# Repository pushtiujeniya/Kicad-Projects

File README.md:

# Kicad-Projects
This repository contains  some 2 layer of PCB module board schematic and layout files designed using kicad software

# BME280 module board
- BME280 module measures pressure, temperature humidity, two mode interface one is I2C and other is SPI so in this design BME280 is interfaced by I2C mode.
- 3.3V DC power supply for operating the board

# DAC module board
- Digital to analog converter using MCP4721 ic
- pull up resistors for i2c  communication protocol SDA and SCL lines
- decoupling capacitor at ouput voltage
- decoupling capacitors at input voltage used MLCC and tantalum as it has low ESR
- 1X5 pin through hole connector to connect the module with controller

# LDO voltage regulator
- AMS1117-3.3V ldo regulator convert 5V DC to 3.3V DC
- Two 1x02 connector for vin and vout
- led indication for voltage input with pretected by 1Kohm resistor
- decoupling capacitor  at voltage input and voltage output

# DHT11  module
- This  module measures the temperature and  humidity value
- DHT11 sensor (input voltage range 3.3V DC to 5.5V DC)
- 3 pin header conenctor for vcc, gnd and data line
- power on led indication with  resistor protection

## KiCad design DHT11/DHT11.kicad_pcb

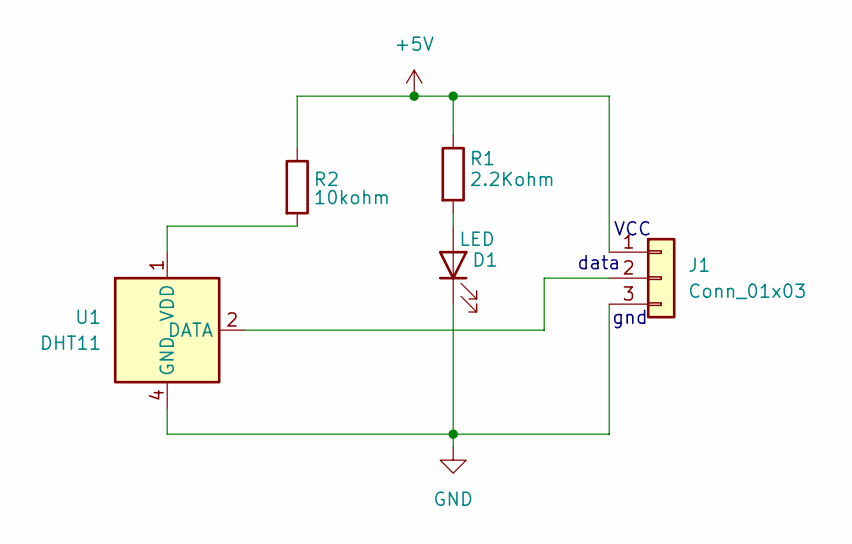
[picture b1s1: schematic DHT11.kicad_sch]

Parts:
D1: LED; LED_0603_1608Metric
J1: Conn_01x03; PinHeader_1x03_P2.54mm_Horizontal
R1: 2.2Kohm; R_0603_1608Metric
R2: 10kohm; R_0603_1608Metric
U1: DHT11; Aosong_DHT11_5.5x12.0_P2.54mm

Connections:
+5V: J1.1, R1.1, R2.1
GND: D1.1 (K), J1.3, U1.4 (GND)
unnamed: D1.2 (A), R1.2
unnamed: J1.2, U1.2 (DATA)
unnamed: R2.2, U1.1 (VDD)

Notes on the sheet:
data
gnd
VCC

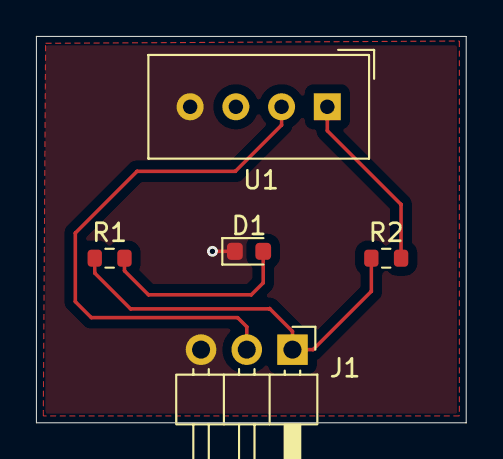
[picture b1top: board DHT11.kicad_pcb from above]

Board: 2 copper layers, 23.9 x 21.5 mm, 5 parts (0 on the bottom side), 5 nets.

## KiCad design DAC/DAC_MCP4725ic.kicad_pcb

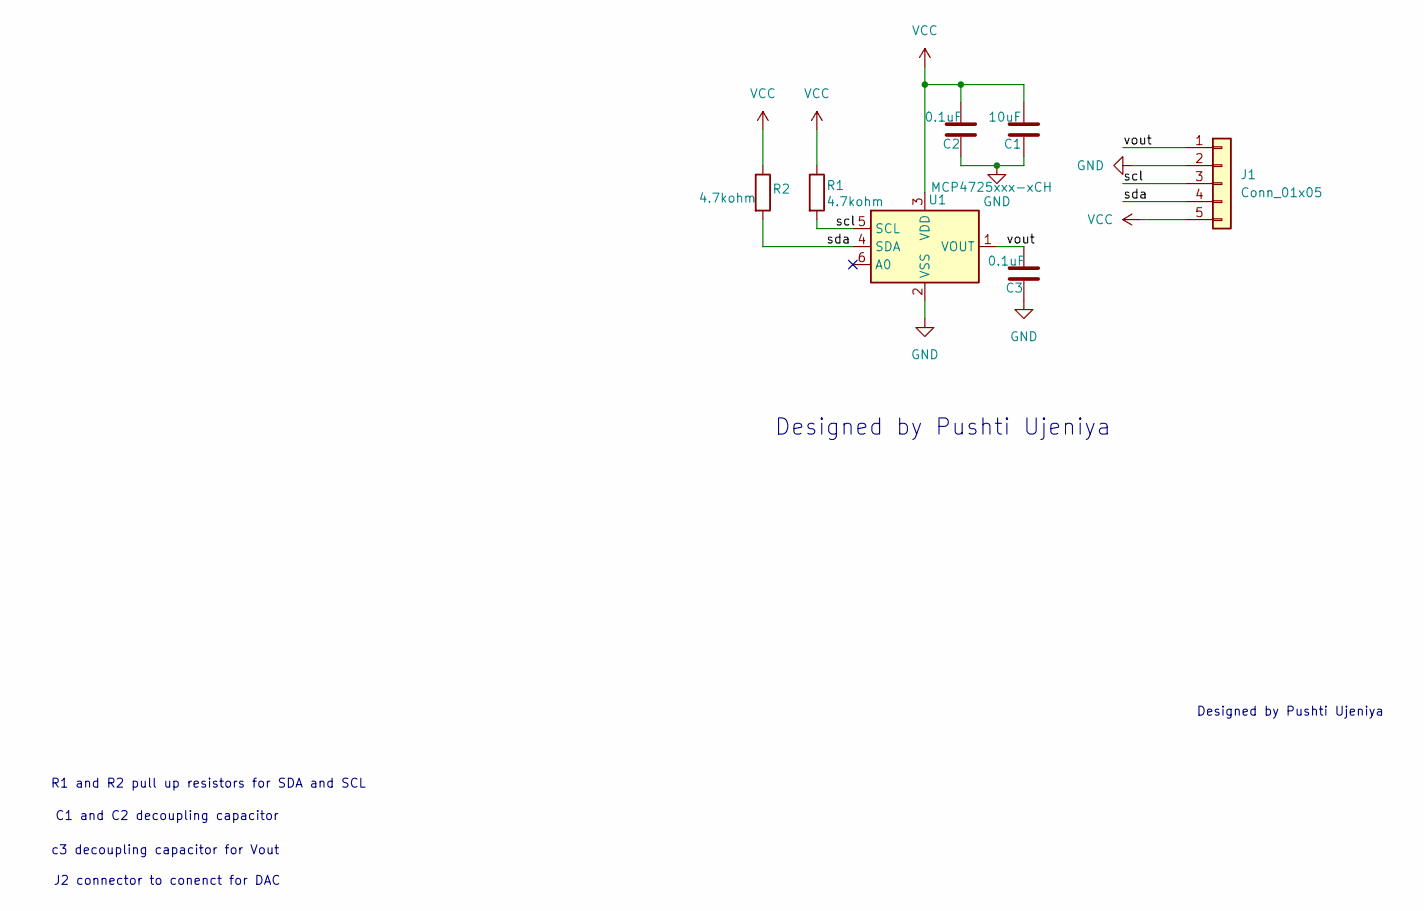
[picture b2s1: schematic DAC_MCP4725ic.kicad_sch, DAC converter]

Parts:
C1: 10uF; CP_EIA-1608-08_AVX-J
C2, C3: 0.1uF; C_0201_0603Metric
J1: Conn_01x05; PinHeader_1x05_P2.54mm_Vertical
R1, R2: 4.7kohm; R_0201_0603Metric
U1: MCP4725xxx-xCH; SOT-23-6

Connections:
/scl: J1.3, R1.2, U1.5 (SCL)
/sda: J1.4, R2.2, U1.4 (SDA)
/vout: C3.2, J1.1, U1.1 (VOUT)
GND: C1.1, C2.1, C3.1, J1.2, U1.2 (VSS)
VCC: C1.2, C2.2, J1.5, R1.1, R2.1, U1.3 (VDD)

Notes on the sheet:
Designed by Pushti Ujeniya
C1 and C2 decoupling capacitor
c3 decoupling capacitor for Vout
J2 connector to conenct for DAC
R1 and R2 pull up resistors for SDA and SCL

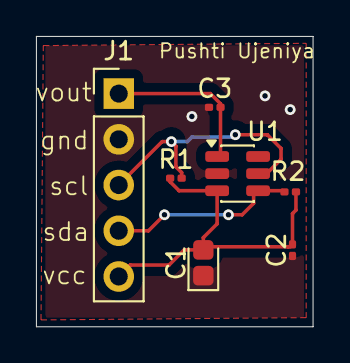
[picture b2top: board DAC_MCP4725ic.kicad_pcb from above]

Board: 2 copper layers, 15.4 x 16.1 mm, 7 parts (0 on the bottom side), 5 nets.

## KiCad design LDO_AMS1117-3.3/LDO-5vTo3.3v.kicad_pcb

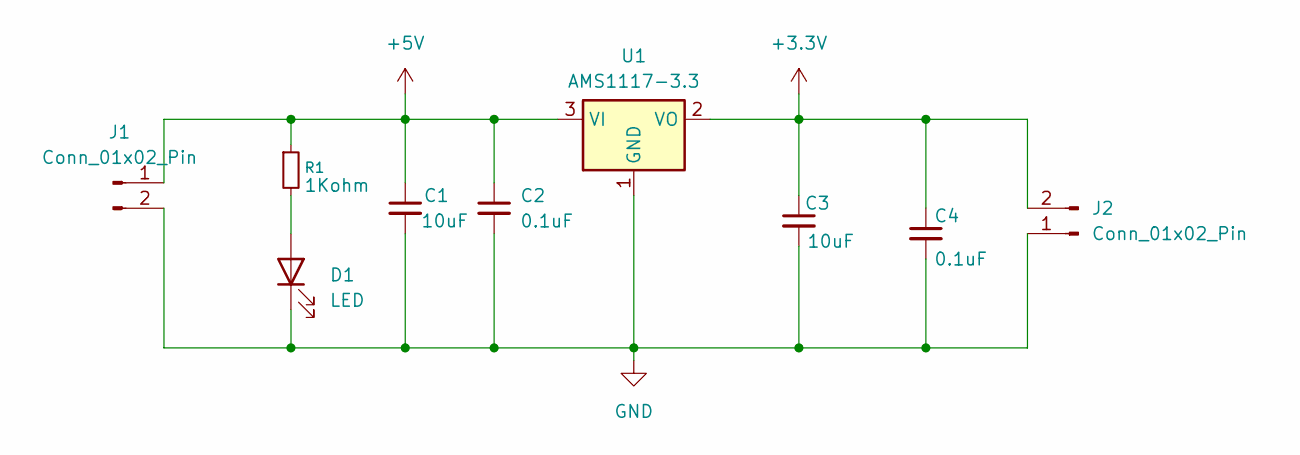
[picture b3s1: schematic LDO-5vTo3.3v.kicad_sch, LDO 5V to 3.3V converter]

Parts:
C1, C3: 10uF; C_0603_1608Metric
C2, C4: 0.1uF; C_0603_1608Metric
D1: LED; LED_0603_1608Metric
J1, J2: Conn_01x02_Pin; PinHeader_1x02_P1.00mm_Vertical
R1: 1Kohm; R_0603_1608Metric
U1: AMS1117-3.3; SOT-223-3_TabPin2

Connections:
+3.3V: C3.1, C4.1, J2.2, U1.2 (VO)
+5V: C1.1, C2.1, J1.1, R1.1, U1.3 (VI)
GND: C1.2, C2.2, C3.2, C4.2, D1.1 (K), J1.2, J2.1, U1.1 (GND)
unnamed: D1.2 (A), R1.2

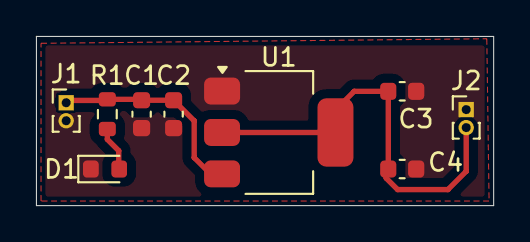
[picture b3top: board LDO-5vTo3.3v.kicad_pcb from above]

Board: 2 copper layers, 25.4 x 9.4 mm, 9 parts (0 on the bottom side), 4 nets.

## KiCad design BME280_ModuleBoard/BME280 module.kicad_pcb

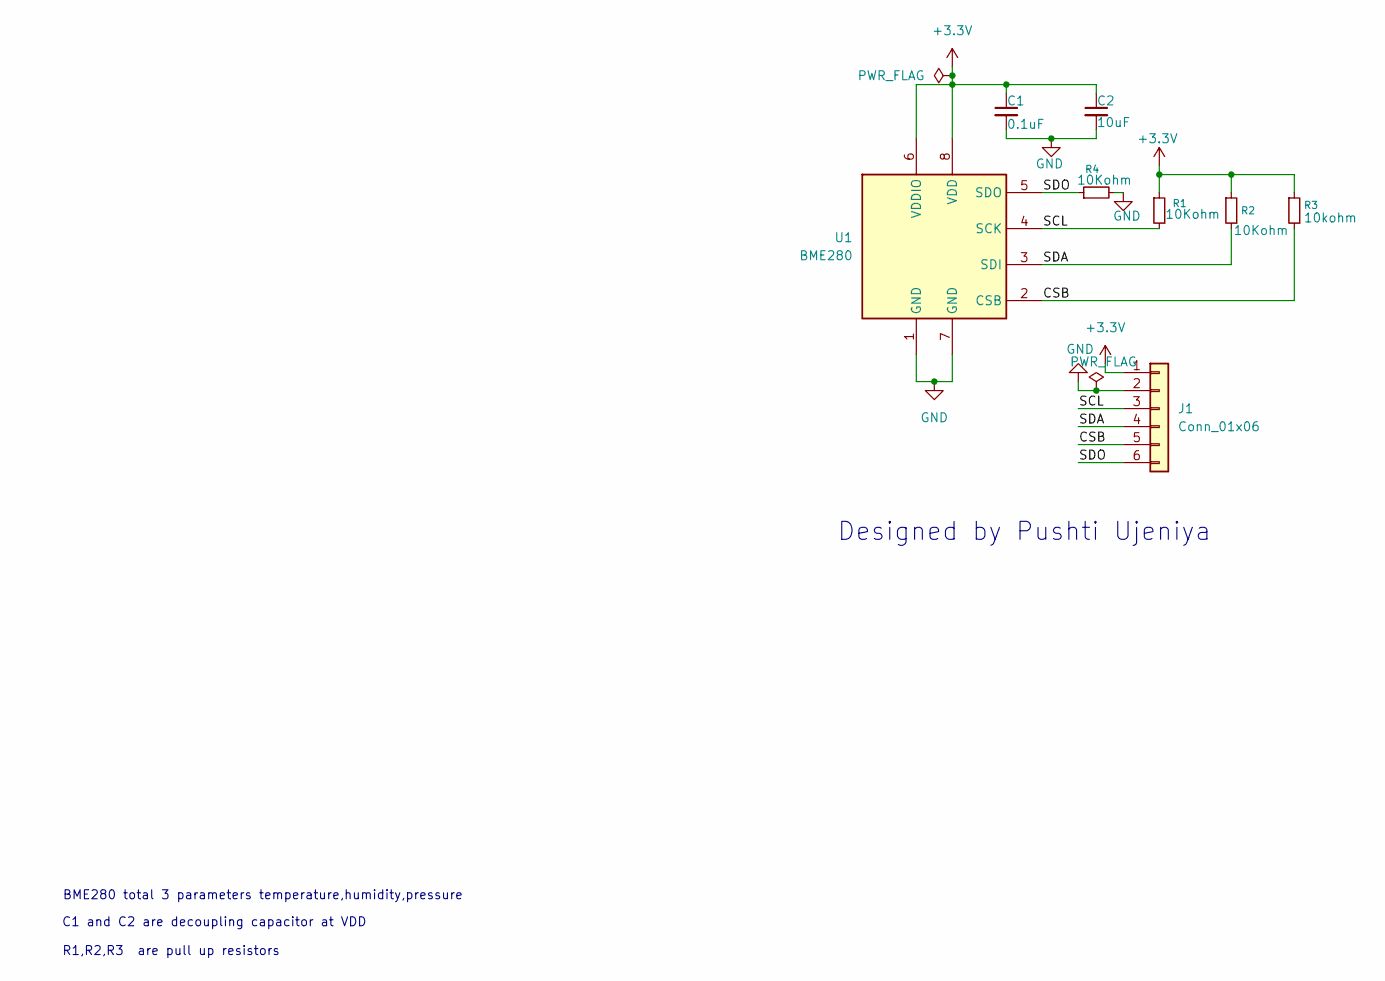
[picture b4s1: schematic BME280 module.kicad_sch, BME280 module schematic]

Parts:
C1: 0.1uF; C_0201_0603Metric
C2: 10uF; CP_EIA-1608-08_AVX-J
J1: Conn_01x06; PinHeader_1x06_P1.00mm_Vertical
R1, R2, R4: 10Kohm; R_0201_0603Metric
R3: 10kohm; R_0201_0603Metric
U1: BME280; Bosch_LGA-8_2.5x2.5mm_P0.65mm_ClockwisePinNumbering

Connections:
+3.3V: C1.1, C2.1, J1.1, R1.1, R2.1, R3.1, U1.6 (VDDIO), U1.8 (VDD)
/CSB: J1.5, R3.2, U1.2 (CSB)
/SCL: J1.3, R1.2, U1.4 (SCK)
/SDA: J1.4, R2.2, U1.3 (SDI)
/SDO: J1.6, R4.1, U1.5 (SDO)
GND: C1.2, C2.2, J1.2, R4.2, U1.1 (GND), U1.7 (GND)

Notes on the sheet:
Designed by Pushti Ujeniya
R1,R2,R3 are pull up resistors
BME280 total 3 parameters temperature,humidity,pressure
C1 and C2 are decoupling capacitor at VDD

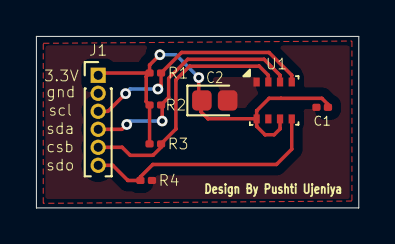
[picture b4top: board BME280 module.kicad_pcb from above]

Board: 2 copper layers, 17.9 x 9.5 mm, 8 parts (0 on the bottom side), 6 nets.

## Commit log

2026-03-16 Schematic file added
2026-03-16 Create BME280 module board
    BME280 module board developed
2026-03-16 temp file
2026-03-16 Created temp
2026-03-16 PCB design layout all layers
2026-03-16 3D images added
2026-03-16 kicad Schematic file
2026-03-16 kicad pcb layout added
2026-03-16 module files added
2026-03-16 BME280 description added
2026-03-17 3d top view image added
2026-03-17 3D side view image added
2026-03-17 Schematic files added
2026-03-17 layout files added
2026-03-18 project overview of DAC board
2026-03-19 3D images added
2026-03-19 LDO module board
2026-03-19 Add LDO voltage regulator section to README
    Added section for LDO voltage regulator with details.
2026-04-01 Add new temporary file
2026-04-01 3D view images added
2026-04-01 schematic view added
2026-04-01 layout image added
2026-04-01 layout file added
2026-04-01 DAC back up added
2026-04-06 Create temp
2026-04-06 Schematic and layout files added
2026-04-06 pcb layout file
2026-04-06 DHT11 module
2026-04-06 Add DHT11 module description to README
    Added details about the DHT11 module including its specifications and features.
